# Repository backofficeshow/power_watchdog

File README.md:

# power_watchdog

Watch the design stream here: https://www.youtube.com/watch?v=kIY5orcxoxM&feature=youtu.be

In its basic incarnation this is for DC voltages, hence a DC input barrel jack that accepts your routers original PSU, and terminals for you to connect an appropriate plug to continue on into your router.

This is an untested design of a WIFI/IOT capable watchdog device. The idea is that it would be connected to your router and it would monitor the health of your network using latency measures / speed check etc and reset your hardware if it falls below a threshold or cannot get the internet at all! Can also operate on a timer.

This is an EAGLE CAD project

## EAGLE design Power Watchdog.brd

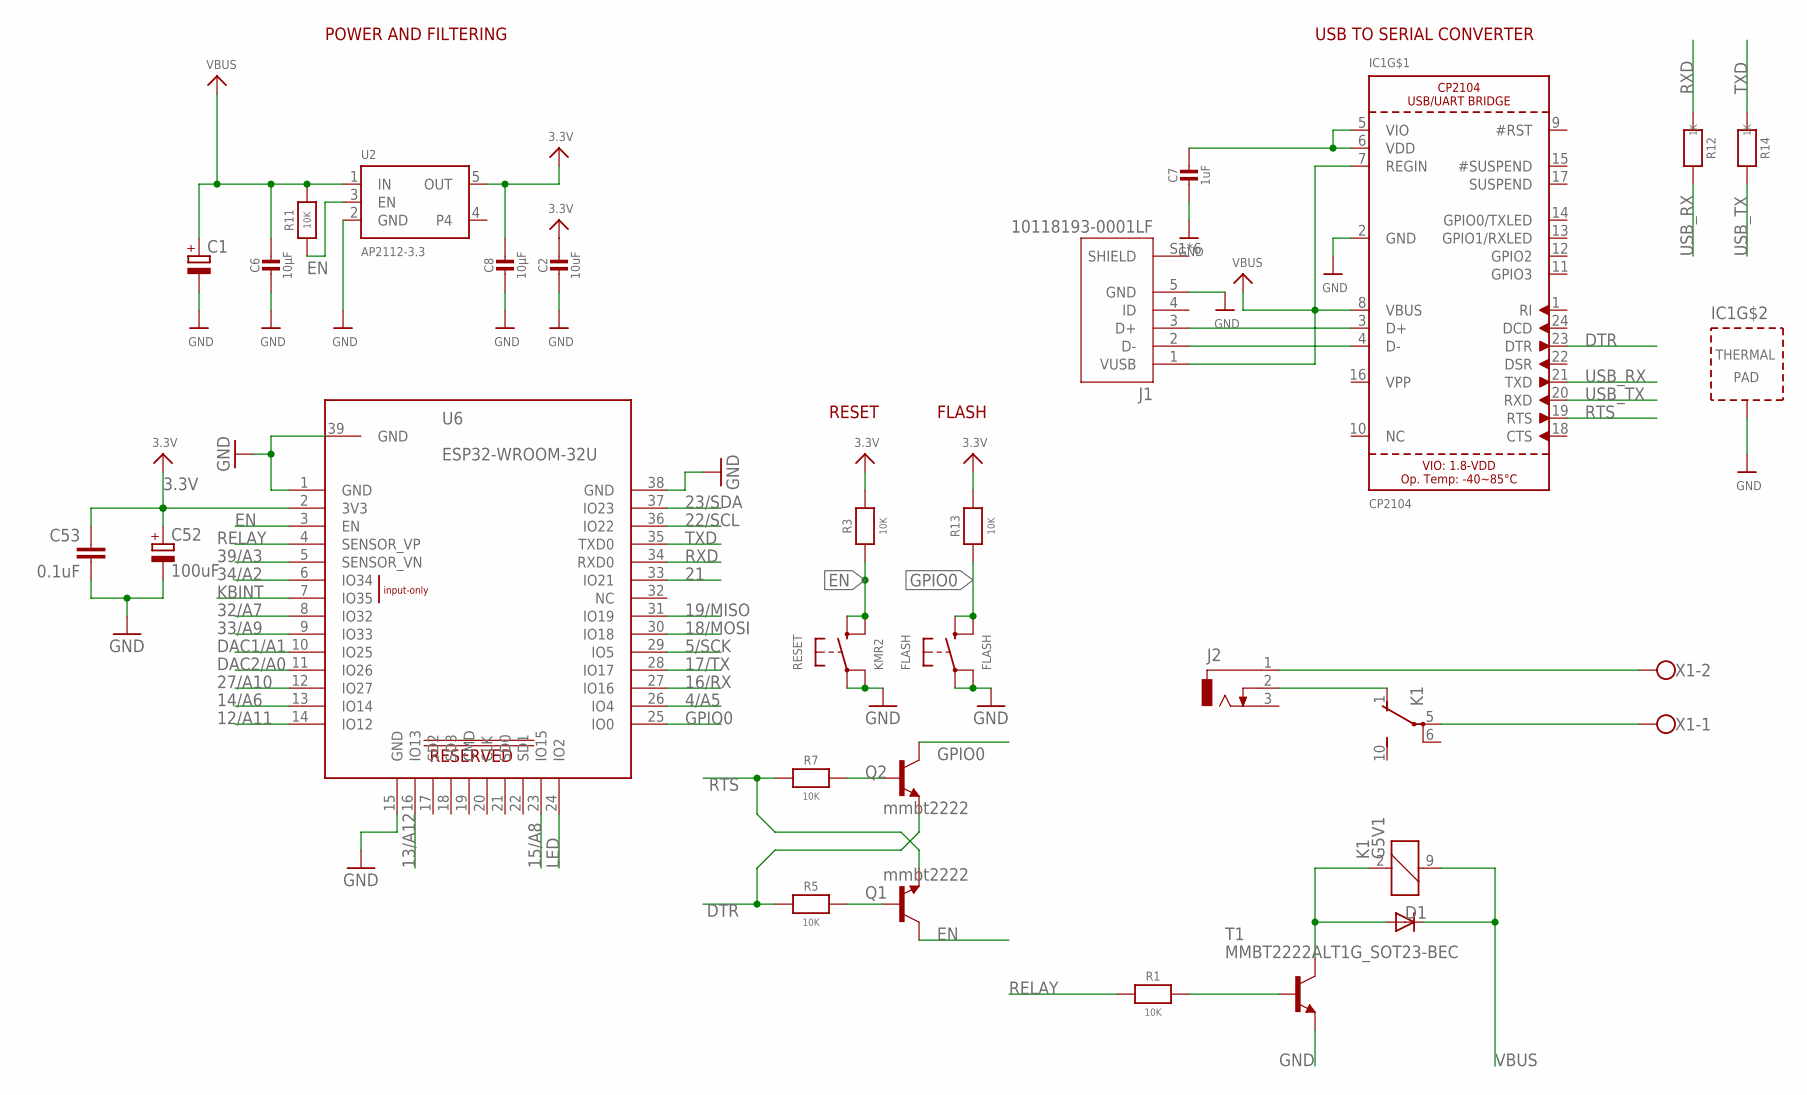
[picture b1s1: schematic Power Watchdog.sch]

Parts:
C1: CPOL-EUE3.5-10; E3,5-10
C2: 10uF; 0805-NO
C6, C8: 10µF; 0805-NO
C7: 1uF; 0603-NO
C52: 100uF; C/6032-28R
C53: 0.1uF; C0603
D1: DIODESMB; SMB-DIODE
FLASH: FLASH; BTN_KMR2_4.6X2.8
IC1: CP2104; QFN24_4MM_SMSC
J1: 10118193-0001LF; FCI_10118193-0001LF
J2: DCJ0303
K1: G5V1
Q1, Q2: mmbt2222; SOT23-3
R1, R3, R5, R7, R11, R13: 10K; 0603-NO
R12, R14: 1K; 0603-NO
RESET: KMR2; BTN_KMR2_4.6X2.8
T1: MMBT2222ALT1G_SOT23-BEC; SOT23-BEC
U2: AP2112-3.3; SOT23-5
U6: ESP32-WROOM-32U; ESP32WROOM32D
X1: W237-102

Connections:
3.3V: C2.1, C8.1, C52.+, C53.1, R3.2, R13.2, U2.5 (OUT), U6.2 (3V3)
4/A5: U6.26 (IO4)
5/SCK: U6.29 (IO5)
12/A11: U6.14 (IO12)
13/A12: U6.16 (IO13)
14/A6: U6.13 (IO14)
15/A8: U6.23 (IO15)
16/RX: U6.27 (IO16)
17/TX: U6.28 (IO17)
18/MOSI: U6.30 (IO18)
19/MISO: U6.31 (IO19)
21: U6.33 (IO21)
22/SCL: U6.36 (IO22)
23/SDA: U6.37 (IO23)
27/A10: U6.12 (IO27)
32/A7: U6.8 (IO32)
33/A9: U6.9 (IO33)
34/A2: U6.6 (IO34)
39/A3: U6.5 (SENSOR_VN)
DAC1/A1: U6.10 (IO25)
DAC2/A0: U6.11 (IO26)
DTR: IC1.23 (DTR), Q2.2 (E), R5.1
EN: Q1.3 (C), R3.1, R11.1, RESET.B (S), RESET.B' (S1), U2.3 (EN), U6.3 (EN)
GND: C1.-, C2.2, C6.2, C7.2, C8.2, C52.-, C53.2, FLASH.A, FLASH.A' (P1), IC1.2 (GND), IC1.THERM (TP), J1.5 (GND), RESET.A, RESET.A' (P1), T1.E, U2.2 (GND), U6.1 (GND), U6.15 (GND), U6.38 (GND), U6.39 (GND)
GPIO0: FLASH.B (S), FLASH.B' (S1), Q2.3 (C), R13.1, U6.25 (IO0)
KBINT: U6.7 (IO35)
LED: U6.24 (IO2)
unnamed: R1.2, T1.B
unnamed: D1.A, K1.2 (1), T1.C
unnamed: J2.1, X1.2
unnamed: J2.2, K1.1 (O)
unnamed: K1.5, X1.1
unnamed: IC1.3 (D+), J1.3 (D+)
unnamed: IC1.4 (D-), J1.2 (D-)
unnamed: C7.1, IC1.5 (VIO), IC1.6 (VDD)
unnamed: Q1.1 (B), R5.2
unnamed: Q2.1 (B), R7.2
RELAY: R1.1, U6.4 (SENSOR_VP)
RTS: IC1.19 (RTS), Q1.2 (E), R7.1
RXD: R12.1, U6.34 (RXD0)
TXD: R14.1, U6.35 (TXD0)
USB_RX: IC1.21 (TXD), R12.2
USB_TX: IC1.20 (RXD), R14.2
VBUS: C1.+, C6.1, D1.C, IC1.7 (REGIN), IC1.8 (VBUS), J1.1 (VUSB), K1.9 (2), R11.2, U2.1 (IN)

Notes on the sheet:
POWER AND FILTERING
RESET
USB TO SERIAL CONVERTER
FLASH
RESERVED

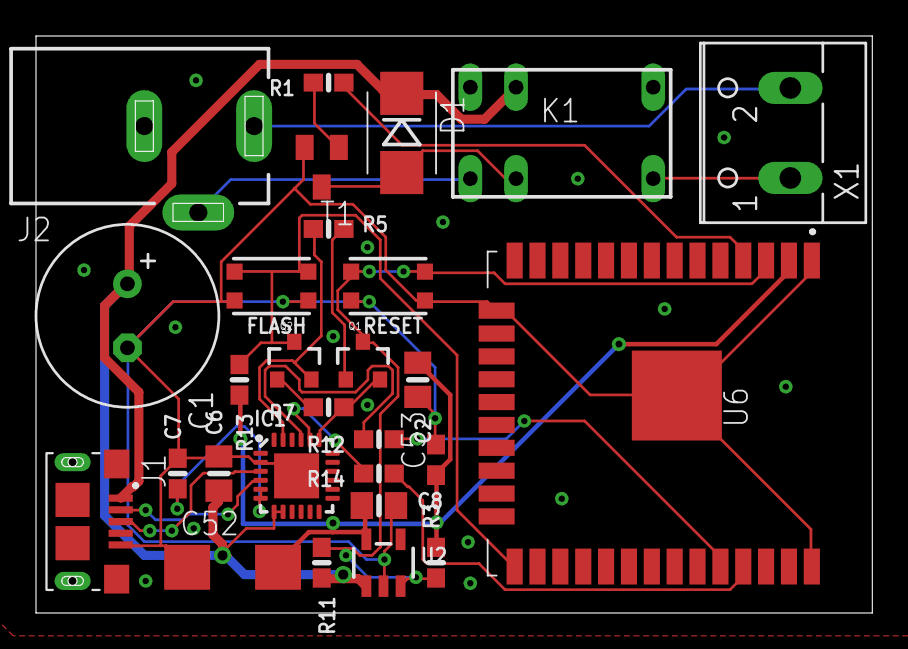
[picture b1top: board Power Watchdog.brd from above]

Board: 2 copper layers, 46.5 x 32.1 mm, 28 parts (0 on the bottom side), 22 nets.

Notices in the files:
parts and their libraries:
oriSparkFun: Licensing: CC v3.0 Share-Alike You are welcome to use this library for commercial purposes.
